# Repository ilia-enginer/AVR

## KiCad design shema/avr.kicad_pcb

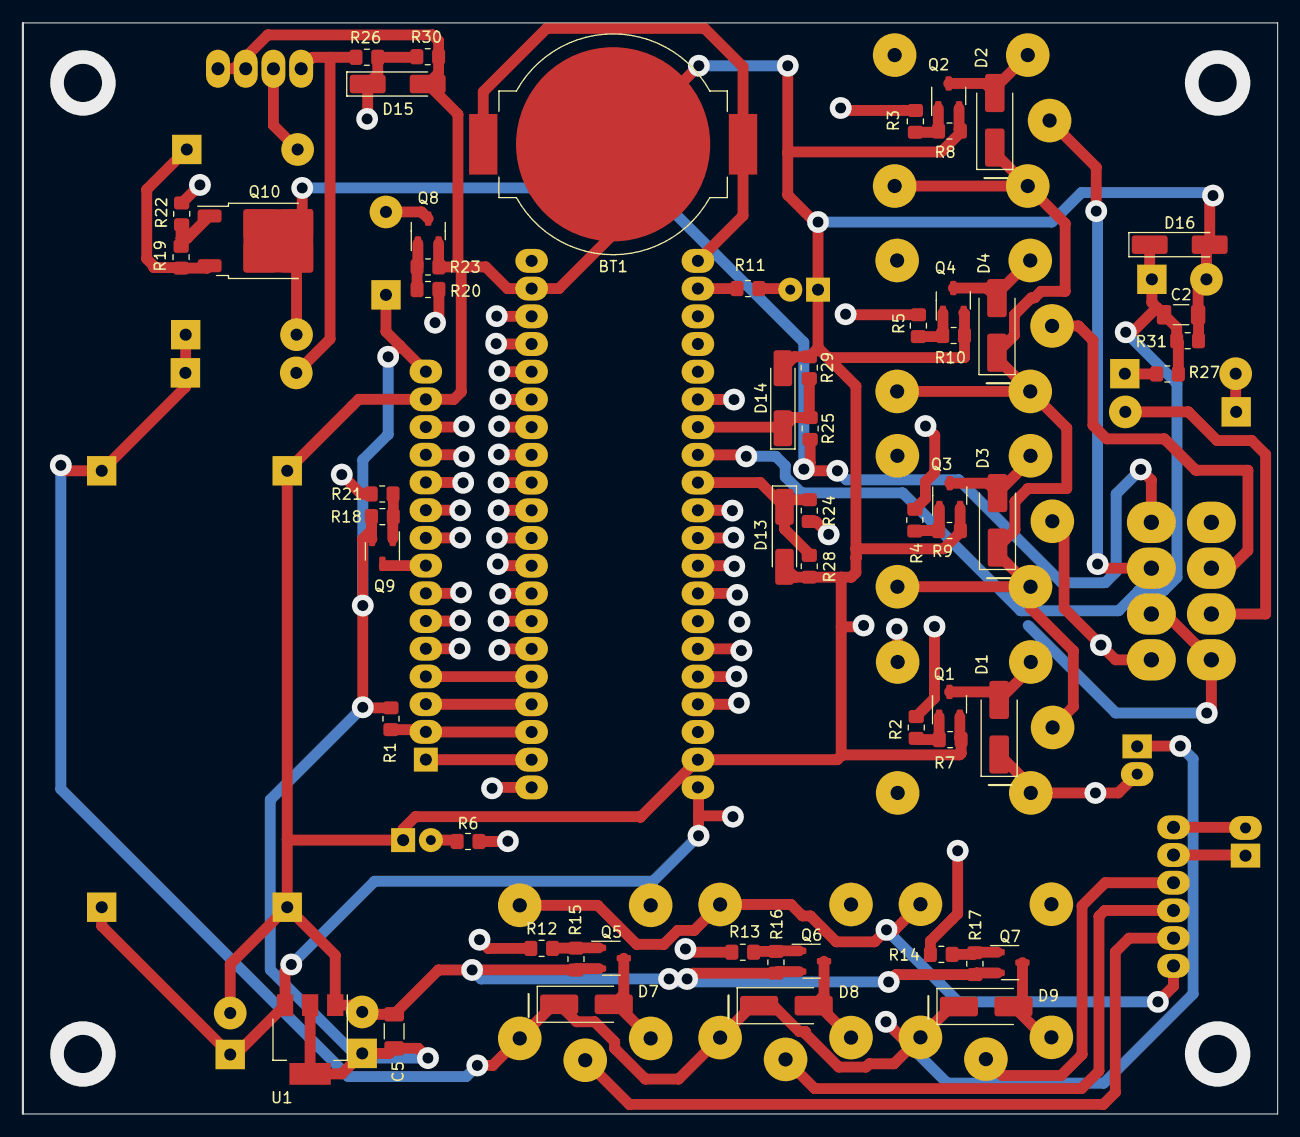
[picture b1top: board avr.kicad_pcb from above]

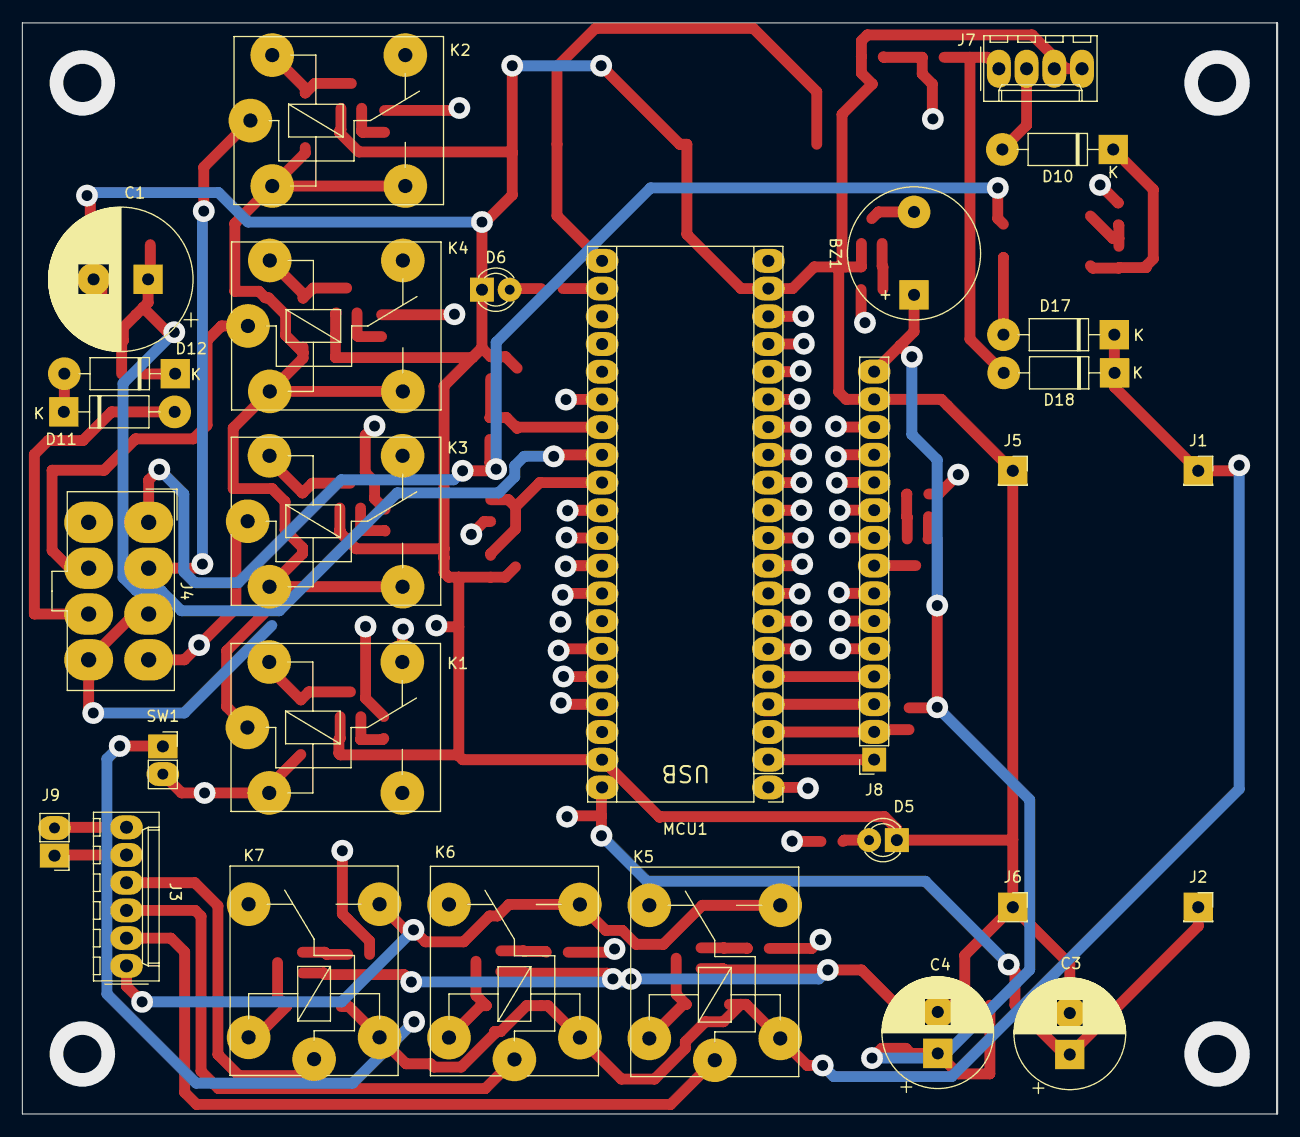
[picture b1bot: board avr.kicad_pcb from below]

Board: 2 copper layers, 115.0 x 100.0 mm, 85 parts (29 on the bottom side), 72 nets.

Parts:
BT1: Battery_Cell; BatteryHolder_MPD_BC2003_1x2032
BZ1: Buzzer; Buzzer_12x9.5RM7.6
C1: 10 uF, 250V; CP_Radial_D13.0mm_P5.00mm
C2, C5: 0.1 uF; C_1206_3216Metric_Pad1.33x1.80mm_HandSolder
C3: 10 uF, 16V; CP_Radial_D10.0mm_P3.80mm
C4: 100 uF, 10V; CP_Radial_D10.0mm_P3.80mm
D1, D2, D3, D4, D7, D8, D9: B340A, SMA; D_SMA_Handsoldering
D5, D6: LED; LED_D3.0mm
D10, D18: 1N5822; D_DO-41_SOD81_P10.16mm_Horizontal
D11, D12, D17: 1N4007; D_DO-41_SOD81_P10.16mm_Horizontal
D13, D14, D15, D16: BZV55B3V3; D_MiniMELF_Handsoldering
J1, J2, J5, J6: Conn_01x01_Pin; PinSocket_1x01_P2.54mm_Vertical
J3: W-06 pitch 2.54mm; Molex_KK-254_AE-6410-06A_1x06_P2.54mm_Vertical
J4: DS1073-01-2x4-MVT6 (MF2x4MA)/DS1073-02-2x4-FCT6 (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; Molex_Mini-Fit_Jr_5566-08A_2x04_P4.20mm_Vertical
J7: W-04 pitch 2.54mm; Molex_KK-254_AE-6410-04A_1x04_P2.54mm_Vertical
J8: TFT_LCD_ST7789V_ILI9488; PinSocket_1x15_P2.54mm_Vertical
J9: Conn_01x02_Pin; PinHeader_1x02_P2.54mm_Vertical
K1, K2, K3, K4, K5, K6, K7: Relay_SPDT; Relay_SPDT_Finder_36.11
MCU1: stm32f4_black_pill; Maple_Mini
Q1, Q2, Q3, Q4, Q5, Q6, Q7, Q8: AO3400A; SOT-23-3
Q9: AO3401A; SOT-23-3
Q10: SUD50P06-15; TO-252-2
R1, R7, R8, R9, R10, R15, R16, R17, R18, R19, R23, R27: 10 kOm; R_0805_2012Metric_Pad1.20x1.40mm_HandSolder
R2, R3, R4, R5, R6, R11, R12, R13, R14, R20, R21, R22: 1 kOm; R_0805_2012Metric_Pad1.20x1.40mm_HandSolder
R24, R25: 3.3 kOm; R_0805_2012Metric_Pad1.20x1.40mm_HandSolder
R26: 5.1 kOm; R_0805_2012Metric_Pad1.20x1.40mm_HandSolder
R28, R29, R30: 910 Om; R_0805_2012Metric_Pad1.20x1.40mm_HandSolder
R31: 470 Om; R_0805_2012Metric_Pad1.20x1.40mm_HandSolder
SW1: SW_DIP_x01; PinSocket_1x02_P2.54mm_Vertical
U1: AMS1117-3.3; SOT-223-3_TabPin2

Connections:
+3.3V: BZ1.1 (-), C4.1, C5.1, J8.15, Q9.2 (S), R1.1, R18.2, U1.2 (VO)
+5V: C3.1, J2.1, MCU1.18 (+5V), MCU1.40 (+5V), U1.3 (VI)
+12L: D7.1 (K), D8.1 (K), D9.1 (K), D17.1 (K), D18.1 (K), J1.1, K5.A1, K6.A1, K7.A1, SW1.1
+12V: D17.2 (A), J4.1, Q10.2 (D), R25.2
BUZ: MCU1.8 (PA11), R20.1
CHARGE_IN: D10.2 (A), J7.2
CHARGE_ON/OFF: MCU1.30 (PA4), R22.1
CHECK_EXT_POWER: D15.1 (K), MCU1.26 (PA0), R26.1, R30.2
CHECK_MOTOR_ACTIVE: C1.1, C2.1, D16.1 (K), MCU1.28 (PA2), R27.1, R31.2
CHECK_MOTOR_ACTIVE_IN: D11.2 (A), J4.7 (Pin_4)
CHECK_RELE_STARTER: D13.1 (K), MCU1.29 (PA3), R24.1, R28.2
CHECK_V_BAT: D14.1 (K), MCU1.27 (PA1), R25.1, R29.2
EXT_V_IN: D18.2 (A), J7.1, R26.2
GND: BT1.2 (-), C1.2, C2.2, C3.2, C4.2, C5.2, D5.1 (K), D6.1 (K), D13.2 (A), D14.2 (A), D15.2 (A), D16.2 (A), J4.3 (Pin_2), J4.8 (Pin_5), J5.1, J6.1, J7.3, J7.4, J8.14, MCU1.19 (GND), MCU1.39 (GND), Q1.2 (S), Q2.2 (S), Q3.2 (S), Q4.2 (S), Q5.2 (S), Q6.2 (S), Q7.2 (S), Q8.2 (S), R7.1, R8.1, R9.1, R10.1, R15.1, R16.1, R17.1, R23.1, R28.1, R29.1, R30.1, R31.1, U1.1 (GND)
K201: J3.5, J9.1
K206: J3.6, J9.2
unnamed: BT1.1 (+), MCU1.21 (VB)
unnamed: BZ1.2 (+), Q8.3 (D)
unnamed: D1.2 (A), K1.A2, Q1.3 (D)
unnamed: D1.1 (K), K1.12, K1.A1, SW1.2
unnamed: D2.2 (A), K2.A2, Q2.3 (D)
unnamed: D3.2 (A), K3.A2, Q3.3 (D)
unnamed: D4.2 (A), K4.A2, Q4.3 (D)
unnamed: D5.2 (A), R6.1
unnamed: D6.2 (A), R11.1
unnamed: D7.2 (A), K5.A2, Q5.3 (D)
unnamed: D8.2 (A), K6.A2, Q6.3 (D)
unnamed: D9.2 (A), K7.A2, Q7.3 (D)
unnamed: D10.1 (K), Q10.3 (S), R19.2
unnamed: D11.1 (K), D12.2 (A)
unnamed: D12.1 (K), R27.2
unnamed: MCU1.9 (PA12), R6.2
unnamed: MCU1.22 (PC13), R11.2
unnamed: Q1.1 (G), R2.2, R7.2
unnamed: Q2.1 (G), R3.2, R8.2
unnamed: Q3.1 (G), R4.2, R9.2
unnamed: Q4.1 (G), R5.2, R10.2
unnamed: Q5.1 (G), R12.2, R15.2
unnamed: Q6.1 (G), R13.2, R16.2
unnamed: Q7.1 (G), R14.2, R17.2
unnamed: Q8.1 (G), R20.2, R23.2
unnamed: Q9.1 (G), R18.1, R21.2
unnamed: Q10.1 (G), R19.1, R22.2
RELE_OBSH: MCU1.11 (PB3), R2.1
RELE_OBSH_OUT: D2.1 (K), D3.1 (K), D4.1 (K), K1.11, K2.14, K2.A1, K3.14, K3.A1, K4.14, K4.A1
RELE_PODSOS: MCU1.14 (PB6), R5.1
RELE_PODSOS_OUT: J4.6, K4.11
RELE_SOST(0): MCU1.15 (PB7), R12.1
RELE_SOST(0)_OUT_K204: J3.2, K5.11
RELE_SOST(1): MCU1.16 (PB8), R13.1
RELE_SOST(1)_OUT_K203: J3.3, K6.11
RELE_SOST(2): MCU1.17 (PB9), R14.1
RELE_SOST(2)_OUT_K205: J3.4, K7.11
RELE_SOST_IN_K202: J3.1, K5.14, K6.14, K7.14
RELE_STARTER: MCU1.13 (PB5), R4.1
RELE_STARTER_OUT: J4.4 (Pin_7), K3.11, R24.2
RELE_ZAJIG: MCU1.12 (PB4), R3.1
RELE_ZAJIG_OUT: J4.2 (Pin_8), K2.11
SD_CS: J8.4, MCU1.5 (PA8)
SPI1_MISO: J8.7, MCU1.32 (PA6)
SPI1_MOSI: J8.10, MCU1.33 (PA7)
SPI1_SCK: J8.9, MCU1.31 (PA5)
SPI2_MISO: J8.2, MCU1.3 (PB14), R1.2
SPI2_MOSI: J8.3, MCU1.4 (PB15)
SPI2_SCK: J8.1, MCU1.2 (PB13)
TFT_CS: J8.13, MCU1.35 (PB1)
TFT_DC: J8.11, MCU1.1 (PB12)
TFT_LED: MCU1.10 (PA15), R21.1
TFT_LED_OUT: J8.8, Q9.3 (D)
TFT_RST: J8.12, MCU1.37 (PB10)
TOUCH_CS: J8.6, MCU1.34 (PB0)
TOUCH_IRQ: J8.5, MCU1.36 (PB2)

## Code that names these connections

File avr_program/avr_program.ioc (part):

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Mcu.Name=STM32F411C(C-E)Ux
Mcu.Package=UFQFPN48
Mcu.UserName=STM32F411CEUx
PA0-WKUP.GPIOParameters=GPIO_Label
PA0-WKUP.GPIO_Label=CHECK_EXT_POWER
PA0-WKUP.Signal=SharedAnalog_PA0
PA1.GPIOParameters=GPIO_Label
PA1.GPIO_Label=CHECK_V_BAT
PA1.Signal=SharedAnalog_PA1
PA10.Signal=USART1_RX
PA11.GPIOParameters=GPIO_PuPd,GPIO_Label,GPIO_ModeDefaultEXTI
PA11.GPIO_Label=TOUCH_IRQ
PA11.GPIO_ModeDefaultEXTI=GPIO_MODE_IT_RISING_FALLING
PA11.GPIO_PuPd=GPIO_PULLUP
PA11.Signal=GPXTI11
PA12.GPIOParameters=GPIO_Label
PA12.GPIO_Label=LED
PA12.Signal=GPIO_Output
PA13.Signal=SYS_JTMS-SWDIO
PA14.Signal=SYS_JTCK-SWCLK
PA15.Signal=S_TIM2_CH1_ETR
PA2.GPIOParameters=GPIO_Label
PA2.GPIO_Label=CHECK_MOTOR_ACTIVE
PA2.Signal=SharedAnalog_PA2
PA3.GPIOParameters=GPIO_Label
PA3.GPIO_Label=CHECK_RELE_STARTER
PA3.Signal=SharedAnalog_PA3
PA4.GPIOParameters=GPIO_Label
PA4.GPIO_Label=CHARGE_ON/OFF
PA4.Signal=GPIO_Output
PA5.Mode=Full_Duplex_Master
PA5.Signal=SPI1_SCK
PA6.Mode=Full_Duplex_Master
PA6.Signal=SPI1_MISO
PA7.Mode=Full_Duplex_Master
PA7.Signal=SPI1_MOSI
PA8.GPIOParameters=GPIO_Label
PA8.GPIO_Label=SD_CS
PA8.Signal=GPIO_Output
PA9.Signal=USART1_TX
PB0.GPIOParameters=GPIO_Label
PB0.GPIO_Label=TOUCH_CS
PB0.Signal=GPIO_Output
PB1.GPIOParameters=GPIO_Label
PB1.GPIO_Label=TFT_CS
PB1.Signal=GPIO_Output
PB10.GPIOParameters=GPIO_Label
PB10.GPIO_Label=TFT_RST
PB10.Signal=GPIO_Output
PB12.GPIOParameters=GPIO_Label
PB12.GPIO_Label=TFT_DC
PB12.Signal=GPIO_Output
PB13.Mode=Full_Duplex_Master
PB13.Signal=SPI2_SCK
PB14.Mode=Full_Duplex_Master
PB14.Signal=SPI2_MISO
PB15.Mode=Full_Duplex_Master
PB15.Signal=SPI2_MOSI
PB3.GPIOParameters=GPIO_Label
PB3.GPIO_Label=RELE_OBSH
PB3.Signal=GPIO_Output
PB4.GPIOParameters=GPIO_Label
PB4.GPIO_Label=RELE_ZAJIG
PB4.Signal=GPIO_Output
PB5.GPIOParameters=GPIO_Label
PB5.GPIO_Label=RELE_STARTER
PB5.Signal=GPIO_Output
PB6.GPIOParameters=GPIO_Label
PB6.GPIO_Label=RELE_PODSOS
PB6.Signal=GPIO_Output
PB7.GPIOParameters=GPIO_Label
PB7.GPIO_Label=RELE_SOST_0
PB7.Signal=GPIO_Output
PB8.GPIOParameters=GPIO_Label
PB8.GPIO_Label=RELE_SOST_1
PB8.Signal=GPIO_Output
PB9.GPIOParameters=GPIO_Label
PB9.GPIO_Label=RELE_SOST_2
PB9.Signal=GPIO_Output
PC13-ANTI_TAMP.GPIOParameters=GPIO_Label
PC13-ANTI_TAMP.GPIO_Label=LED_ERROR
PC13-ANTI_TAMP.Signal=GPIO_Output
PC14-OSC32_IN.Mode=LSE-External-Oscillator
PC14-OSC32_IN.Signal=RCC_OSC32_IN
PC15-OSC32_OUT.Mode=LSE-External-Oscillator
PC15-OSC32_OUT.Signal=RCC_OSC32_OUT
PH0\ -\ OSC_IN.Mode=HSE-External-Oscillator
PH0\ -\ OSC_IN.Signal=RCC_OSC_IN
PH1\ -\ OSC_OUT.Mode=HSE-External-Oscillator
PH1\ -\ OSC_OUT.Signal=RCC_OSC_OUT
RCC.HSE_VALUE=25000000
RCC.SYSCLKFreq_VALUE=100000000
RCC.SYSCLKSource=RCC_SYSCLKSOURCE_PLLCLK
board=custom
